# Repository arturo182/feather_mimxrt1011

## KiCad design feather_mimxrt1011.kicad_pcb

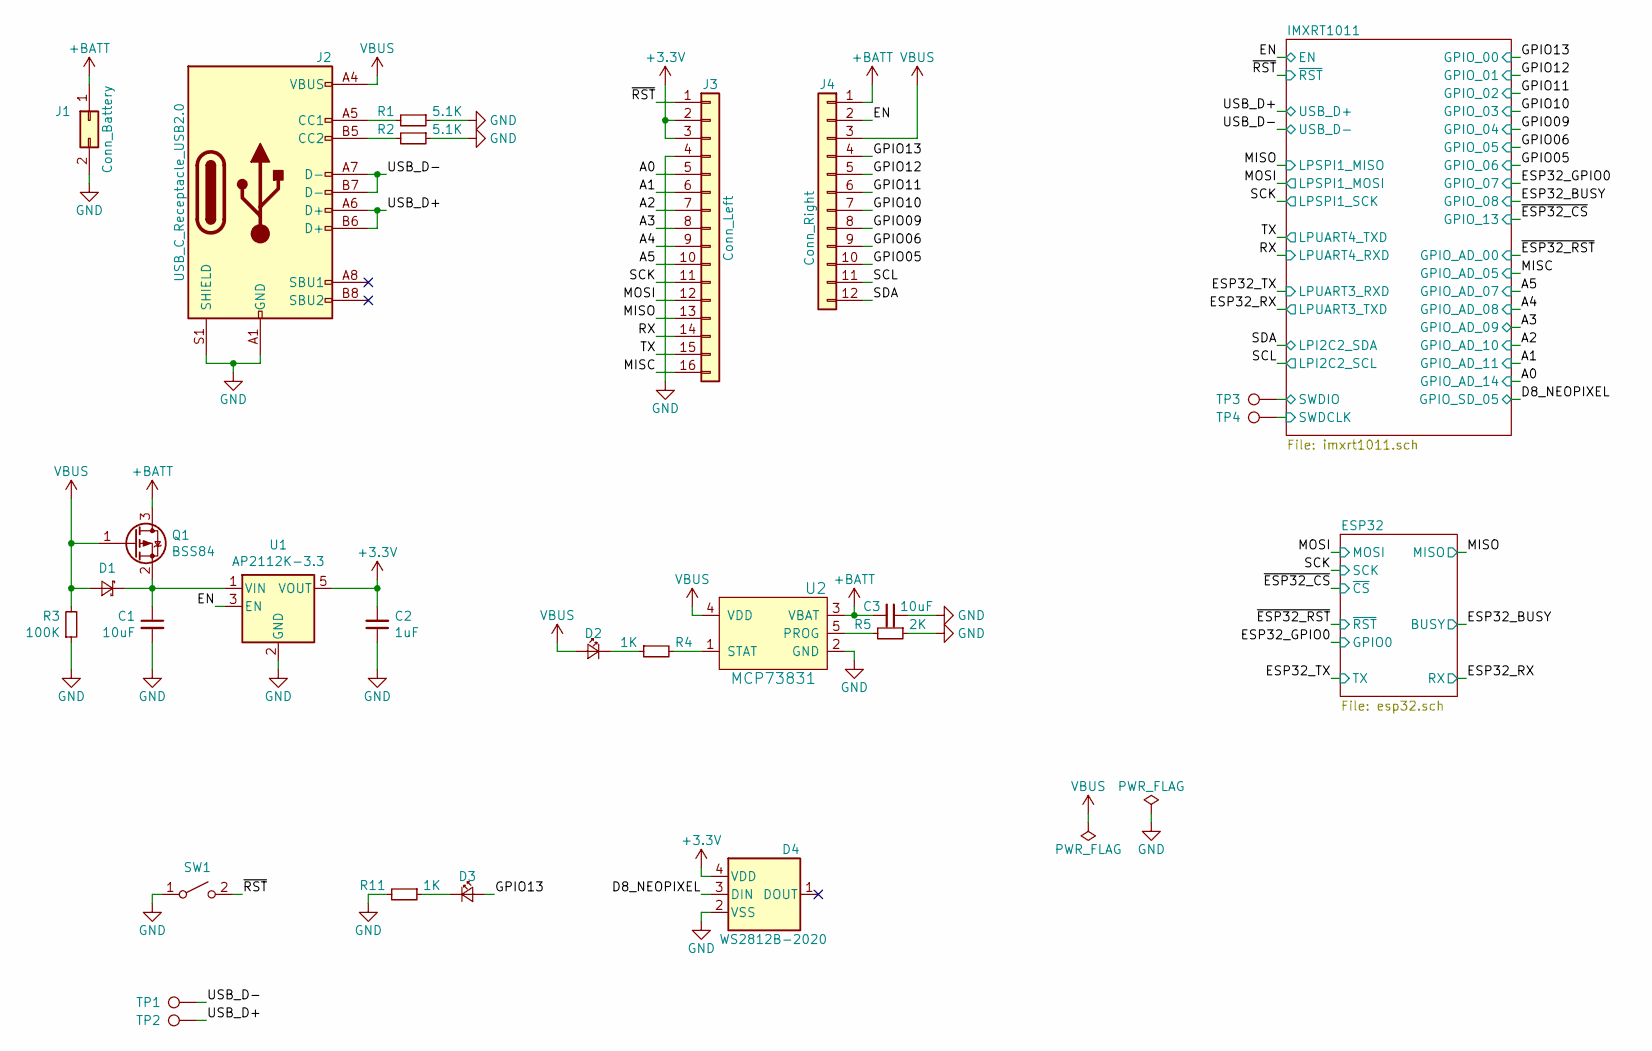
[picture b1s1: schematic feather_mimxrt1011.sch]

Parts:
C1, C3: 10uF; C_0402_1005Metric
C2: 1uF; C_0402_1005Metric
D1: D_Schottky_Small; D_SOD-323; LCSC C114023
D2: LED_CHR; LED_0603_1608Metric
D3: LED_USR; LED_0603_1608Metric
D4: WS2812B-2020
J1: Conn_Battery; JST_PH_S2B-PH-SM4-TB_1x02-1MP_P2.00mm_Horizontal; LCSC C375128
J2: USB_C_Receptacle_USB2.0; USB_C_Receptacle_HRO_TYPE-C-31-M-12; LCSC C319148
J3: Conn_Left; PinSocket_1x16_P2.54mm_Vertical
J4: Conn_Right; PinSocket_1x12_P2.54mm_Vertical
Q1: BSS84; SOT-23; LCSC C85202
R1, R2: 5.1K; R_0402_1005Metric
R3: 100K; R_0402_1005Metric
R4, R11: 1K; R_0402_1005Metric
R5: 2K; R_0402_1005Metric
SW1: SW_RST; SW_SPST_B3U-1000P-B; LCSC C128937
TP1: TP_USB_D-; TestPoint_Pad_D1.0mm
TP2: TP_USB_D+; TestPoint_Pad_D1.0mm
TP3: TP_SWDIO; TestPoint_Pad_D1.0mm
TP4: TP_SWDCLK; TestPoint_Pad_D1.0mm
U1: AP2112K-3.3; SOT-23-5; LCSC C51118
U2: MCP73831; SOT-23-5; LCSC C14879

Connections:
+3V3: C2.2, D4.4 (VDD), J3.2, J3.3, U1.5 (VOUT); also elsewhere on the board
+BATT: C3.2, J1.1, J4.1, Q1.3 (D), U2.3 (VBAT)
/A0: J3.5; also elsewhere on the board
/A1: J3.6; also elsewhere on the board
/A2: J3.7; also elsewhere on the board
/A3: J3.8; also elsewhere on the board
/A4: J3.9; also elsewhere on the board
/A5: J3.10; also elsewhere on the board
/D8_NEOPIXEL: D4.3 (DIN); also elsewhere on the board
/EN: J4.2, U1.3 (EN); also elsewhere on the board
/GPIO05: J4.10; also elsewhere on the board
/GPIO06: J4.9; also elsewhere on the board
/GPIO09: J4.8; also elsewhere on the board
/GPIO10: J4.7; also elsewhere on the board
/GPIO11: J4.6; also elsewhere on the board
/GPIO12: J4.5; also elsewhere on the board
/GPIO13: D3.2 (A), J4.4; also elsewhere on the board
/MISC: J3.16; also elsewhere on the board
/MISO: J3.13; also elsewhere on the board
/MOSI: J3.12; also elsewhere on the board
/RX: J3.14; also elsewhere on the board
/SCK: J3.11; also elsewhere on the board
/SCL: J4.11; also elsewhere on the board
/SDA: J4.12; also elsewhere on the board
/SWDCLK: TP4.1; also elsewhere on the board
/SWDIO: TP3.1; also elsewhere on the board
/TX: J3.15; also elsewhere on the board
/USB_D+: J2.A6 (D+), J2.B6 (D+), TP2.1; also elsewhere on the board
/USB_D-: J2.A7 (D-), J2.B7 (D-), TP1.1; also elsewhere on the board
/~RST~: J3.1, SW1.2 (B); also elsewhere on the board
GND: C1.2, C2.1, C3.1, D4.2 (VSS), J1.2, J2.A1 (GND), J2.A12 (GND), J2.B1 (GND), J2.B12 (GND), J2.S1 (SHIELD), J3.4, R1.1, R2.1, R3.1, R5.1, R11.2, SW1.1 (A), U1.2 (GND), U2.2 (GND); also elsewhere on the board
unnamed 44: C1.1, D1.1 (K), Q1.2 (S), U1.1 (VIN); also elsewhere on the board
unnamed: D2.1 (K), R4.1
unnamed: D3.1 (K), R11.1
unnamed: J2.A5 (CC1), R1.2
unnamed: J2.B5 (CC2), R2.2
unnamed: R4.2, U2.1 (STAT)
unnamed: R5.2, U2.5 (PROG)
VBUS: D1.2 (A), D2.2 (A), J2.A4 (VBUS), J2.A9 (VBUS), J2.B4 (VBUS), J2.B9 (VBUS), J4.3, Q1.1 (G), R3.2, U2.4 (VDD); also elsewhere on the board

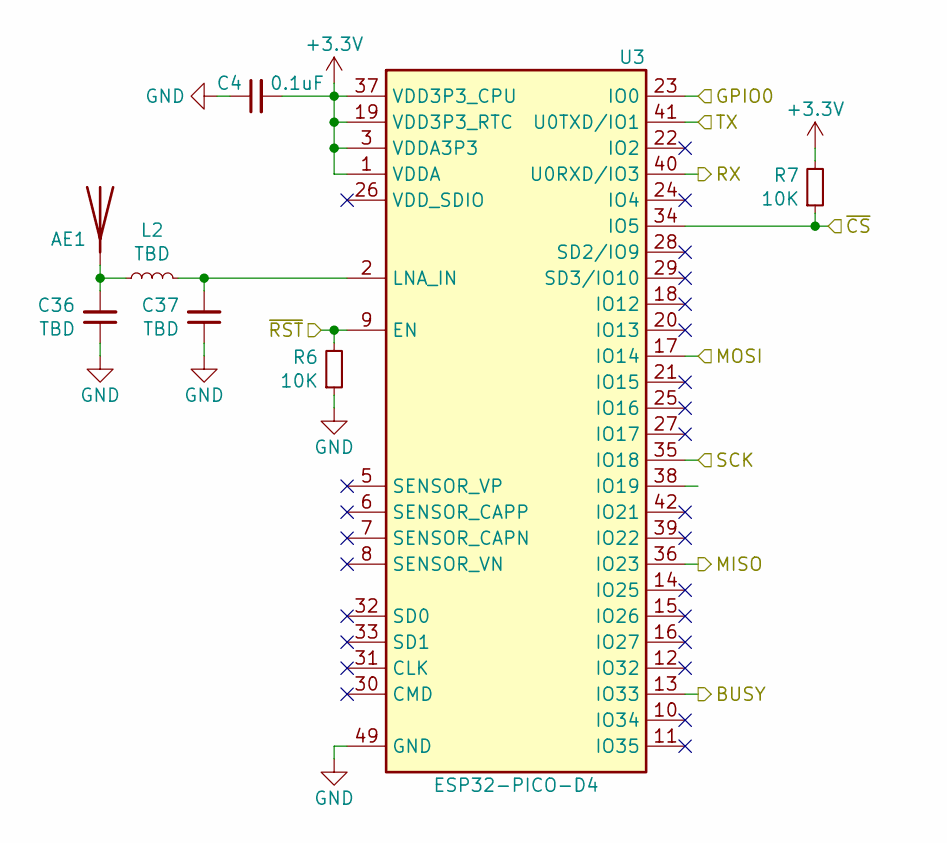
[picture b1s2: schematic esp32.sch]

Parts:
AE1: 2450AT42B100; Johanson_2450AT42B100; Mouser 609-2450AT42B100E
C4: 0.1uF; C_0402_1005Metric
C36, C37: TBD; C_0402_1005Metric
L2: TBD; L_0402_1005Metric
R6, R7: 10K; R_0402_1005Metric
U3: ESP32-PICO-D4; QFN-48-1EP_7x7mm_P0.5mm_EP5.3x5.3mm; LCSC C193707

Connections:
+3V3: C4.2, R7.2, U3.1 (VDDA), U3.3 (VDDA3P3), U3.4 (VDDA3P3), U3.19 (VDD3P3_RTC), U3.37 (VDD3P3_CPU), U3.43 (VDDA), U3.46 (VDDA); also elsewhere on the board
/ESP32_BUSY: U3.13 (IO33); also elsewhere on the board
/ESP32_GPIO0: U3.23 (IO0); also elsewhere on the board
/ESP32_RX: U3.40 (U0RXD/IO3); also elsewhere on the board
/ESP32_TX: U3.41 (U0TXD/IO1); also elsewhere on the board
/MISO: U3.36 (IO23); also elsewhere on the board
/MOSI: U3.17 (IO14); also elsewhere on the board
/SCK: U3.35 (IO18); also elsewhere on the board
/~ESP32_CS~: R7.1, U3.34 (IO5); also elsewhere on the board
/~ESP32_RST~: R6.2, U3.9 (EN); also elsewhere on the board
GND: C4.1, C36.1, C37.1, R6.1, U3.49 (GND); also elsewhere on the board
unnamed: AE1.1, C36.2, L2.1
unnamed: C37.2, L2.2, U3.2 (LNA_IN)

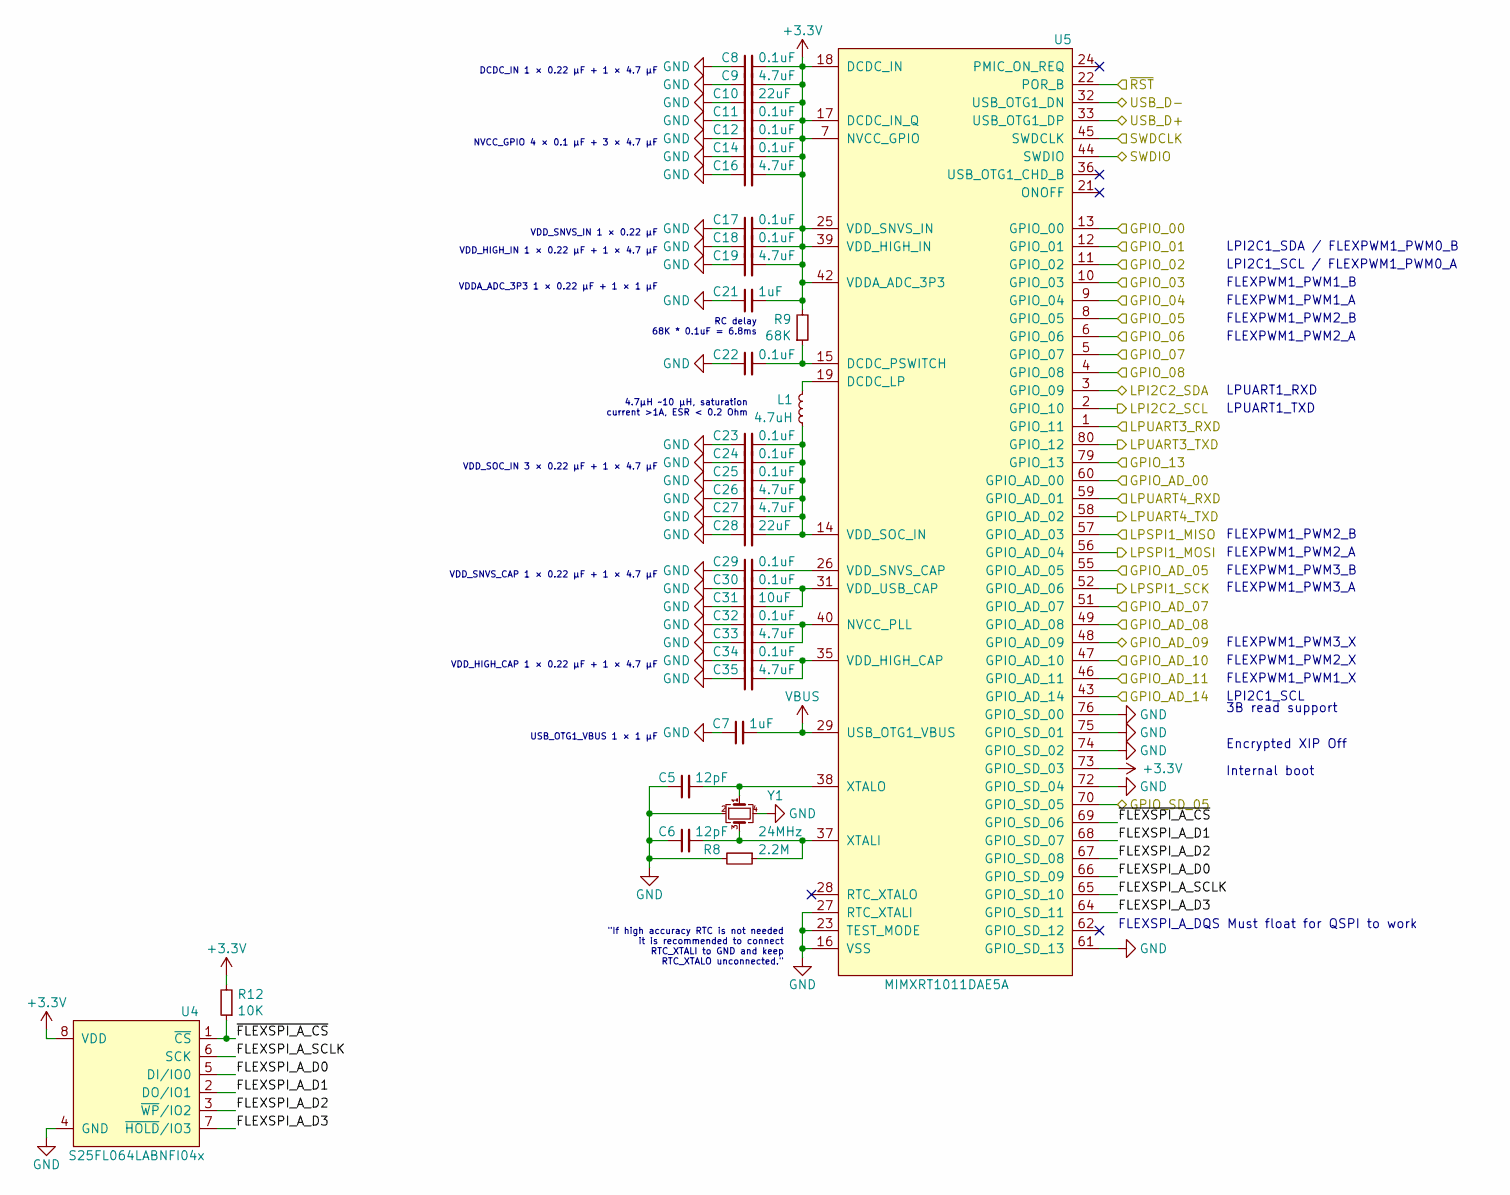
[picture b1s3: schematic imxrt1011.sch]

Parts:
C5, C6: 12pF; C_0402_1005Metric
C7, C21: 1uF; C_0402_1005Metric
C8, C11, C12, C14, C17, C18, C22, C23, C24, C25, C29, C30, C32, C34: 0.1uF; C_0402_1005Metric
C9, C16, C19, C26, C27, C33, C35: 4.7uF; C_0402_1005Metric
C10, C28: 22uF; C_0603_1608Metric
C31: 10uF; C_0402_1005Metric
L1: 4.7uH; L_0806_2012Metric; LCSC C98036
R8: 2.2M; R_0402_1005Metric
R9: 68K; R_0402_1005Metric
R12: 10K; R_0402_1005Metric
U4: S25FL064LABNFI04x; WSON-8-1EP_6x5mm_P1.27mm_EP3.4x4mm; Mouser 727-S25FL064LABNF040
U5: MIMXRT1011DAE5A; TQFP-80_12x12mm_P0.5mm; Mouser 771-MIMXRT1011DAE5A
Y1: 24MHz; Crystal_SMD_2016-4Pin_2.0x1.6mm; LCSC C389789

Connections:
+3V3: C8.2, C9.2, C10.2, C11.2, C12.2, C14.2, C16.2, C17.2, C18.2, C19.2, C21.2, R9.2, R12.2, U4.8 (VDD), U5.7 (NVCC_GPIO), U5.17 (DCDC_IN_Q), U5.18 (DCDC_IN), U5.25 (VDD_SNVS_IN), U5.39 (VDD_HIGH_IN), U5.42 (VDDA_ADC_3P3), U5.50 (NVCC_GPIO), U5.63 (NVCC_GPIO), U5.71 (NVCC_GPIO), U5.73 (GPIO_SD_03); also elsewhere on the board
/A0: U5.43 (GPIO_AD_14); also elsewhere on the board
/A1: U5.46 (GPIO_AD_11); also elsewhere on the board
/A2: U5.47 (GPIO_AD_10); also elsewhere on the board
/A3: U5.48 (GPIO_AD_09); also elsewhere on the board
/A4: U5.49 (GPIO_AD_08); also elsewhere on the board
/A5: U5.51 (GPIO_AD_07); also elsewhere on the board
/D8_NEOPIXEL: U5.70 (GPIO_SD_05); also elsewhere on the board
/ESP32_BUSY: U5.4 (GPIO_08); also elsewhere on the board
/ESP32_GPIO0: U5.5 (GPIO_07); also elsewhere on the board
/ESP32_RX: U5.80 (GPIO_12); also elsewhere on the board
/ESP32_TX: U5.1 (GPIO_11); also elsewhere on the board
/GPIO05: U5.6 (GPIO_06); also elsewhere on the board
/GPIO06: U5.8 (GPIO_05); also elsewhere on the board
/GPIO09: U5.9 (GPIO_04); also elsewhere on the board
/GPIO10: U5.10 (GPIO_03); also elsewhere on the board
/GPIO11: U5.11 (GPIO_02); also elsewhere on the board
/GPIO12: U5.12 (GPIO_01); also elsewhere on the board
/GPIO13: U5.13 (GPIO_00); also elsewhere on the board
/IMXRT1011/FLEXSPI_A_D0: U4.5 (DI/IO0), U5.66 (GPIO_SD_09)
/IMXRT1011/FLEXSPI_A_D1: U4.2 (DO/IO1), U5.68 (GPIO_SD_07)
/IMXRT1011/FLEXSPI_A_D2: U4.3 (~WP~/IO2), U5.67 (GPIO_SD_08)
/IMXRT1011/FLEXSPI_A_D3: U4.7 (~HOLD~/IO3), U5.64 (GPIO_SD_11)
/IMXRT1011/FLEXSPI_A_SCLK: U4.6 (SCK), U5.65 (GPIO_SD_10)
/IMXRT1011/~FLEXSPI_A_CS~: R12.1, U4.1 (~CS~), U5.69 (GPIO_SD_06)
/MISC: U5.55 (GPIO_AD_05); also elsewhere on the board
/MISO: U5.57 (GPIO_AD_03); also elsewhere on the board
/MOSI: U5.56 (GPIO_AD_04); also elsewhere on the board
/RX: U5.59 (GPIO_AD_01); also elsewhere on the board
/SCK: U5.52 (GPIO_AD_06); also elsewhere on the board
/SCL: U5.2 (GPIO_10); also elsewhere on the board
/SDA: U5.3 (GPIO_09); also elsewhere on the board
/SWDCLK: U5.45 (SWDCLK); also elsewhere on the board
/SWDIO: U5.44 (SWDIO); also elsewhere on the board
/TX: U5.58 (GPIO_AD_02); also elsewhere on the board
/USB_D+: U5.33 (USB_OTG1_DP); also elsewhere on the board
/USB_D-: U5.32 (USB_OTG1_DN); also elsewhere on the board
/~ESP32_CS~: U5.79 (GPIO_13); also elsewhere on the board
/~ESP32_RST~: U5.60 (GPIO_AD_00); also elsewhere on the board
/~RST~: U5.22 (POR_B); also elsewhere on the board
GND: C5.1, C6.1, C7.1, C8.1, C9.1, C10.1, C11.1, C12.1, C14.1, C16.1, C17.1, C18.1, C19.1, C21.1, C22.1, C23.1, C24.1, C25.1, C26.1, C27.1, C28.1, C29.1, C30.1, C31.1, C32.1, C33.1, C34.1, C35.1, R8.2, U4.4 (GND), U4.9 (GND), U5.16 (VSS), U5.20 (DCDC_GND), U5.23 (TEST_MODE), U5.27 (RTC_XTALI), U5.30 (VSS), U5.34 (NGND_KEL0), U5.41 (VSSA_ADC_3P3), U5.54 (VSS), U5.61 (GPIO_SD_13), U5.72 (GPIO_SD_04), U5.74 (GPIO_SD_02), U5.75 (GPIO_SD_01), U5.76 (GPIO_SD_00), U5.78 (VSS), Y1.2, Y1.4; also elsewhere on the board
unnamed: C5.2, U5.38 (XTALO), Y1.1
unnamed: C6.2, R8.1, U5.37 (XTALI), Y1.3
unnamed: C22.2, R9.1, U5.15 (DCDC_PSWITCH)
unnamed: C23.2, C24.2, C25.2, C26.2, C27.2, C28.2, L1.1, U5.14 (VDD_SOC_IN), U5.53 (VDD_SOC_IN), U5.77 (VDD_SOC_IN)
unnamed: C29.2, U5.26 (VDD_SNVS_CAP)
unnamed: C30.2, C31.2, U5.31 (VDD_USB_CAP)
unnamed: C32.2, C33.2, U5.40 (NVCC_PLL)
unnamed: C34.2, C35.2, U5.35 (VDD_HIGH_CAP)
unnamed: L1.2, U5.19 (DCDC_LP)
VBUS: C7.2, U5.29 (USB_OTG1_VBUS); also elsewhere on the board

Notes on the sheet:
VDD_HIGH_IN 1 × 0.22 μF + 1 × 4.7 μF
4.7µH ~~10 µH, saturation current >1A, ESR < 0.2 Ohm
VDD_HIGH_CAP 1 × 0.22 μF + 1 × 4.7 μF
DCDC_IN 1 × 0.22 μF + 1 × 4.7 μF
VDD_SNVS_CAP 1 × 0.22 μF + 1 × 4.7 μF
"If high accuracy RTC is not needed it is recommended to connect RTC_XTALI to GND and keep RTC_XTALO unconnected."
RC delay 68K * 0.1uF = 6.8ms
VDDA_ADC_3P3 1 × 0.22 μF + 1 × 1 μF
NVCC_GPIO 4 × 0.1 μF + 3 × 4.7 μF
VDD_SNVS_IN 1 × 0.22 μF
USB_OTG1_VBUS 1 × 1 μF
FLEXSPI_A_DQS Must float for QSPI to work
VDD_SOC_IN 3 × 0.22 μF + 1 × 4.7 μF
FLEXPWM1_PWM2_A
FLEXPWM1_PWM2_B
FLEXPWM1_PWM3_A
FLEXPWM1_PWM1_X
LPUART1_TXD
FLEXPWM1_PWM1_B
FLEXPWM1_PWM1_A
FLEXPWM1_PWM3_X
FLEXPWM1_PWM2_X
LPI2C1_SCL
FLEXPWM1_PWM3_B
LPI2C1_SDA / FLEXPWM1_PWM0_B
LPI2C1_SCL / FLEXPWM1_PWM0_A
LPUART1_RXD
Internal boot
Encrypted XIP Off
3B read support

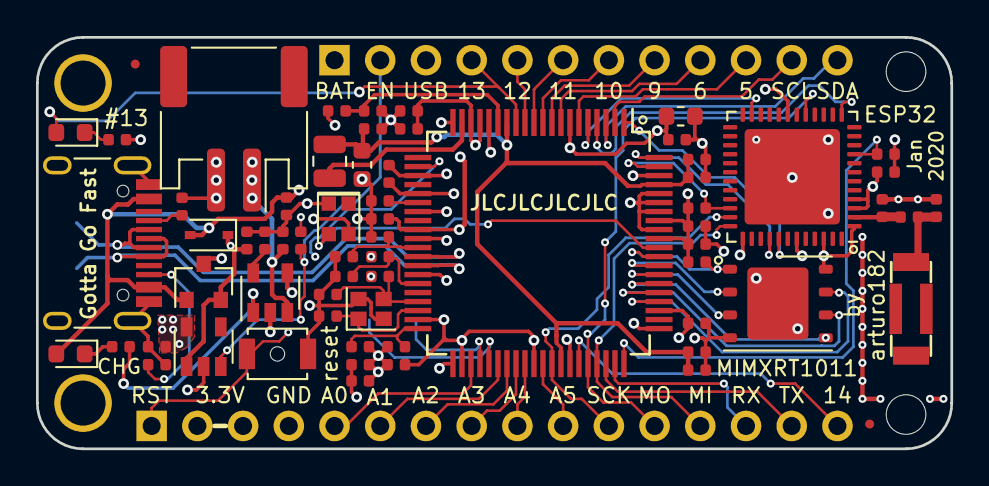
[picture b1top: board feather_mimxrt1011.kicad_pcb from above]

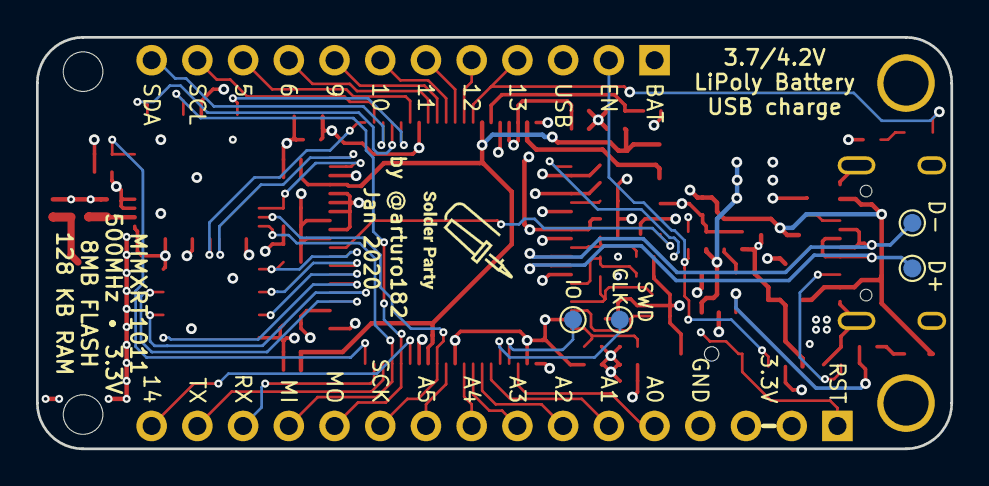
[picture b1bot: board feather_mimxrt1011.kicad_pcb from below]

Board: 4 copper layers, 50.8 x 22.9 mm, 69 parts (4 on the bottom side), 62 nets.

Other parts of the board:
R10: 100K; R_0402_1005Metric

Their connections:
/EN: R10.1; also elsewhere on the board
unnamed 44: R10.2; also elsewhere on the board

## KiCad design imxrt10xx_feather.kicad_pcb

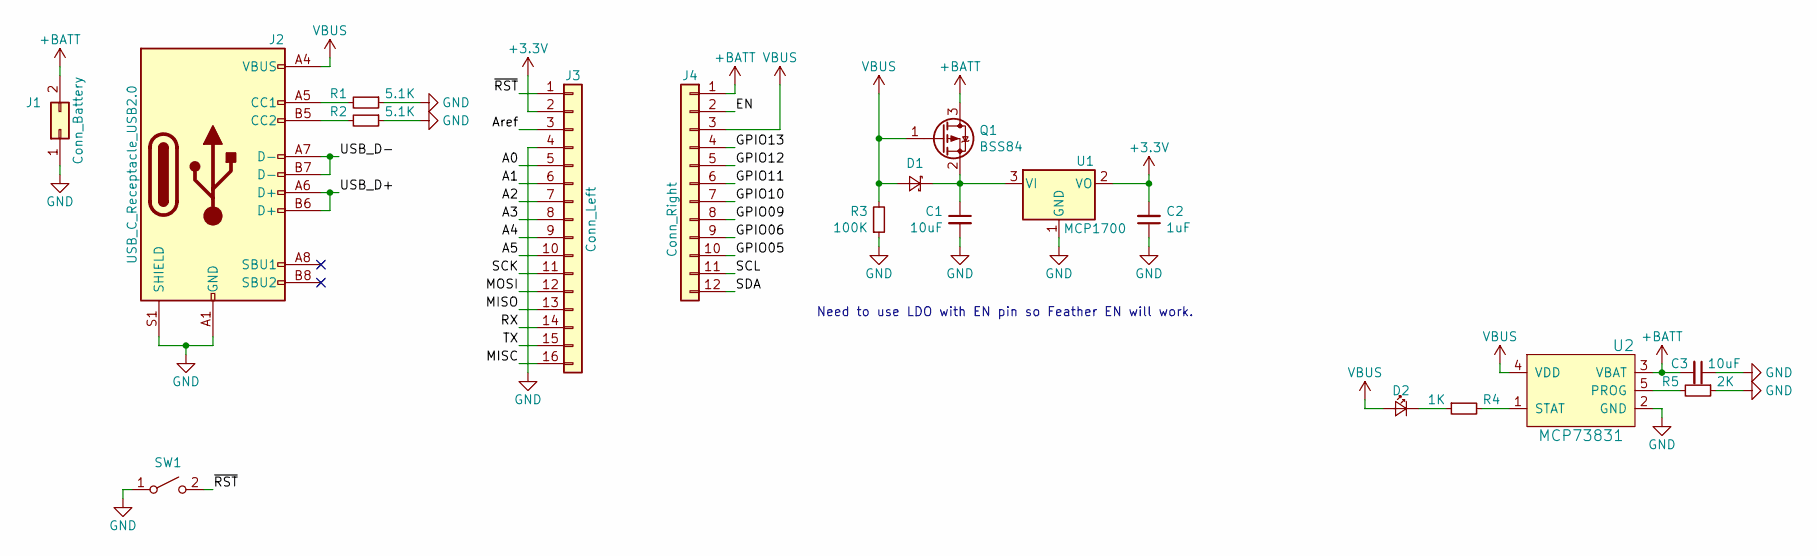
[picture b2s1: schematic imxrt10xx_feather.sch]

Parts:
C1, C3: 10uF; C_0603_1608Metric
C2: 1uF; C_0603_1608Metric
D1: D_Schottky_Small; D_SOD-323_HandSoldering
D2: LED_CHR; LED_0603_1608Metric
J1: Conn_Battery; JST_PH_S2B-PH-SM4-TB_1x02-1MP_P2.00mm_Horizontal
J2: USB_C_Receptacle_USB2.0; USB_C_Receptacle_HRO_TYPE-C-31-M-12
J3: Conn_Left; PinSocket_1x16_P2.54mm_Vertical
J4: Conn_Right; PinSocket_1x12_P2.54mm_Vertical
Q1: BSS84; SOT-23
R1, R2: 5.1K; R_0603_1608Metric
R3: 100K; R_0603_1608Metric
R4: 1K; R_0603_1608Metric
R5: 2K; R_0603_1608Metric
SW1: SW_RST; SW_SPST_B3U-1000P-B
U1: MCP1700; SOT-23
U2: MCP73831; SOT-23-5

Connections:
+3V3: C2.2, J3.2, U1.2 (VO)
+BATT: C3.2, J1.2, J4.1, Q1.3 (D), U2.3 (VBAT)
/A0: J3.5
/A1: J3.6
/A2: J3.7
/A3: J3.8
/A4: J3.9
/A5: J3.10
/Aref: J3.3
/EN: J4.2
/GPIO05: J4.10
/GPIO06: J4.9
/GPIO09: J4.8
/GPIO10: J4.7
/GPIO11: J4.6
/GPIO12: J4.5
/GPIO13: J4.4
/MISC: J3.16
/MISO: J3.13
/MOSI: J3.12
/RX: J3.14
/SCK: J3.11
/SCL: J4.11
/SDA: J4.12
/TX: J3.15
/USB_D+: J2.A6 (D+), J2.B6 (D+)
/USB_D-: J2.A7 (D-), J2.B7 (D-)
/~RST~: J3.1, SW1.2 (B)
GND: C1.2, C2.1, C3.1, J1.1, J2.A1 (GND), J2.A12 (GND), J2.B1 (GND), J2.B12 (GND), J2.S1 (SHIELD), J3.4, R1.1, R2.1, R3.1, R5.1, SW1.1 (A), U1.1 (GND), U2.2 (GND)
unnamed: C1.1, D1.1 (K), Q1.2 (S), U1.3 (VI)
unnamed: D2.1 (K), R4.1
unnamed: J2.A5 (CC1), R1.2
unnamed: J2.B5 (CC2), R2.2
unnamed: R4.2, U2.1 (STAT)
unnamed: R5.2, U2.5 (PROG)
VBUS: D1.2 (A), D2.2 (A), J2.A4 (VBUS), J2.A9 (VBUS), J2.B4 (VBUS), J2.B9 (VBUS), J4.3, Q1.1 (G), R3.2, U2.4 (VDD)

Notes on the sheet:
Need to use LDO with EN pin so Feather EN will work.

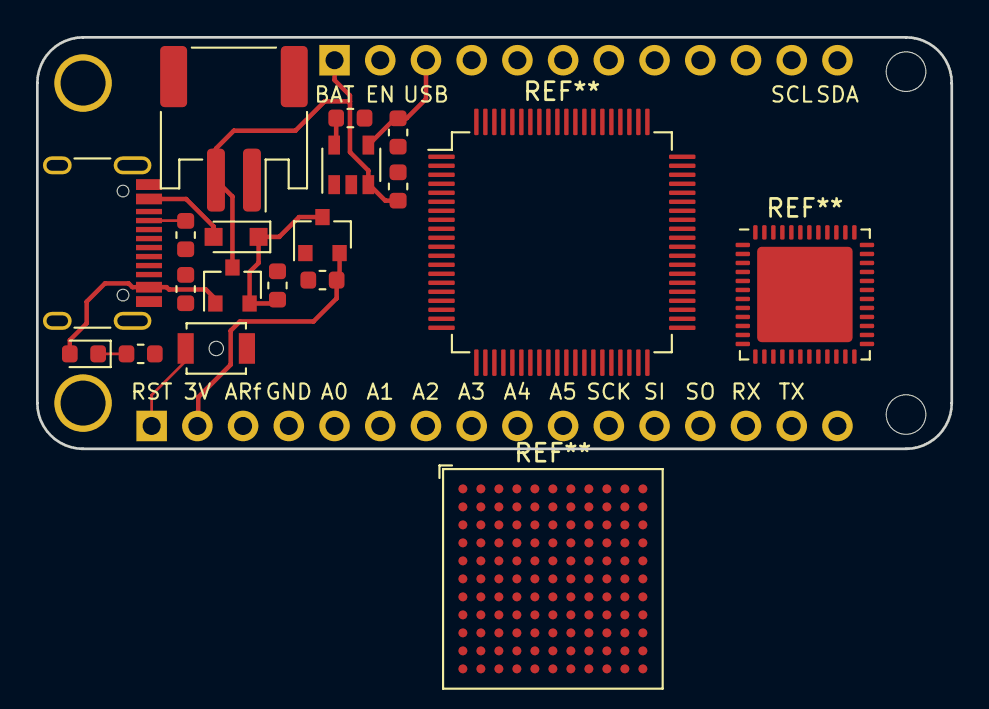
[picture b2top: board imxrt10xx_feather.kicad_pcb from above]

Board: 2 copper layers, 50.8 x 22.9 mm, 18 parts (0 on the bottom side), 13 nets.

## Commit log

2019-11-04 Initial import
2020-01-10 Rev 1
2020-01-10 Rename to a friendlier project name
2020-03-11 Rev 2
